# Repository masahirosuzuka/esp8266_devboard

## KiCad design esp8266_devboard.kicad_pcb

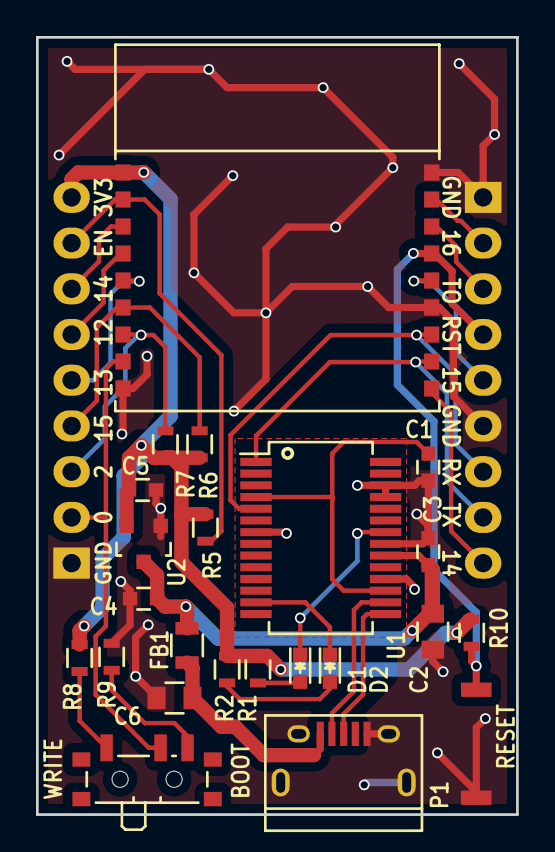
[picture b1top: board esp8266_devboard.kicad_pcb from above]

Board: 2 copper layers, 26.7 x 43.2 mm, 25 parts (0 on the bottom side), 27 nets.

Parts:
C1, C3: 100nF; C_0603
C2: 4.7uF; C_0805
C4, C5: 10uF; C_0603
C6: 10uF; C_0805
D1, D2: LED; LED-0603
FB1: 600mA; R_0805
P1: USB_OTG; USB_Micro-B
P2, P3: CONN_01X09; Pin_Header_Straight_1x09
R1, R2: 270R; R_0603
R5, R6, R7, R8, R9, R10: 10k; R_0603
SW1: MODE; SW_SPDT_PCM12
SW2: RESET; b3u_1110
U1: FT232R; SSOP-28_5.3x10.2mm_Pitch0.65mm
U2: XC6206; SOT-23
U3: esp-wroom-02

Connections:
+3V3: C5.1, P2.9, R1.1, R2.1, R5.1, R6.1, R7.1, R8.1, R10.1, U2.2, U3.1
+5V: C2.1, C3.1, C4.1, FB1.2, U1.20, U2.3
/CBUS1: D1.1, U1.22
/CBUS2: D2.1, U1.13
/EN: P2.8, R5.2, U3.2
/GPIO0: P2.2, SW1.2, U3.8
/GPIO2: P2.3, R7.2, U3.7
/GPIO4: P3.9, U3.10
/GPIO5: P3.5, U3.14
/GPIO12: P2.6, U3.4
/GPIO13: P2.5, U3.5
/GPIO14: P2.7, U3.3
/GPIO15: P2.4, R6.2, U3.6
/GPIO16: P3.2, U3.17
/RST: P3.4, R10.2, SW2.2, U3.15
/RX-TX: P3.7, U1.5, U3.12
/TOUT: P3.3, U3.16
/TX-RX: P3.8, U1.1, U3.11
/USBDM: P1.2, U1.16
/USBDP: P1.3, U1.15
GND: C1.2, C2.2, C3.2, C4.2, C5.2, C6.2, P1.5, P1.6, P2.1, P3.1, P3.6, R9.2, SW2.1, U1.7, U1.18, U1.21, U1.25, U1.26, U2.1, U3.9, U3.13, U3.18
unnamed: C1.1, U1.4, U1.17
unnamed: C6.1, FB1.1, P1.1
unnamed: D1.2, R1.2
unnamed: D2.2, R2.2
unnamed: R8.2, SW1.1
unnamed: R9.1, SW1.3

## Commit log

2015-12-31 add OSHW symbol
2016-01-03 commit before change FT230X to FT232R
2016-01-09 Finish replacing FT232R
2016-01-11 modify pattern and silk
2016-02-11 remove ft230.lib
